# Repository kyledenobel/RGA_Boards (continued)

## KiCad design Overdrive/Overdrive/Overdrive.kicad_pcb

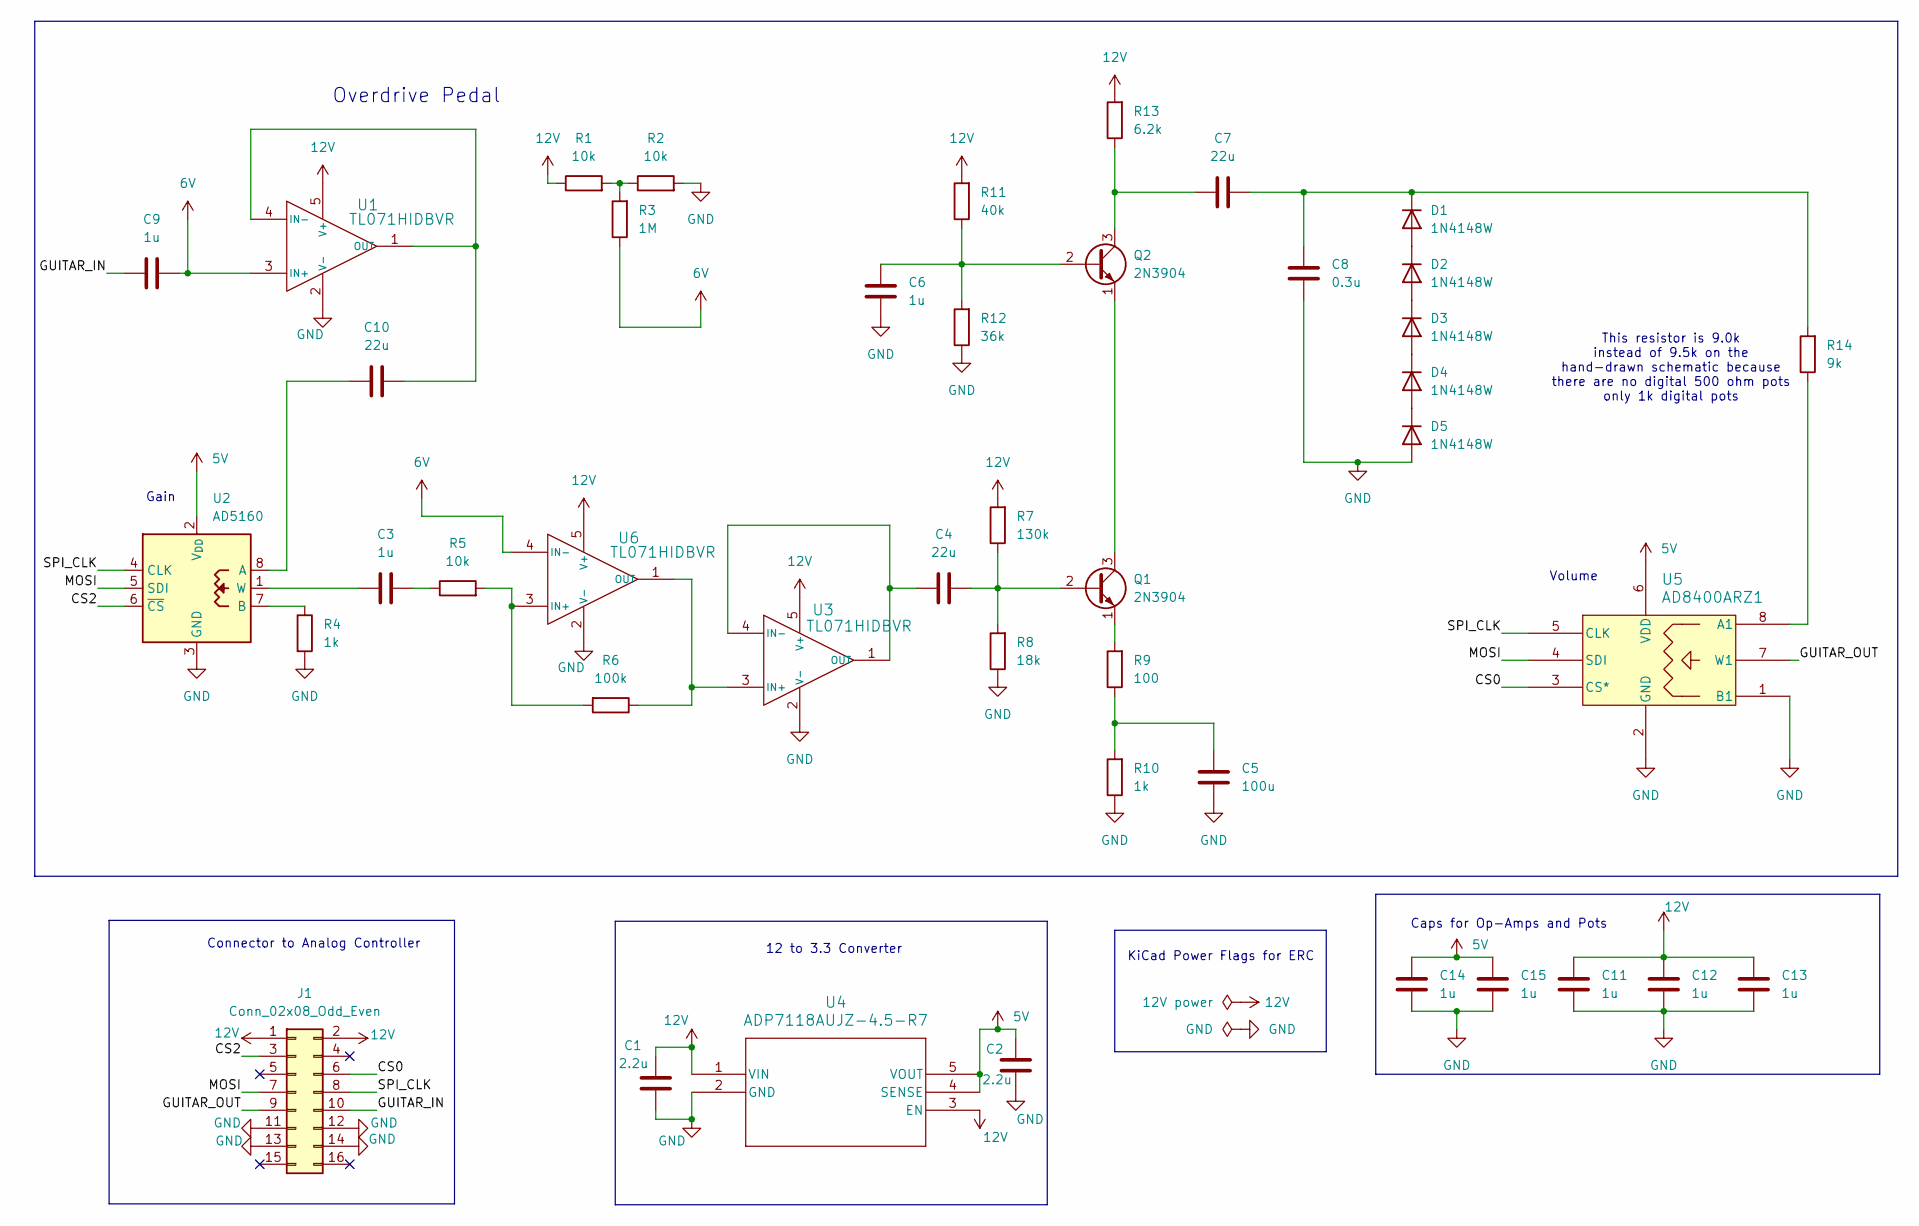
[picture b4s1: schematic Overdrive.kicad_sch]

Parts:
C1, C2: 2.2u; C_0603_1608Metric
C3, C6, C9, C11, C12, C13, C14, C15: 1u; C_0603_1608Metric
C4, C7, C10: 22u; C_0603_1608Metric
C5: 100u; C_1206_3216Metric
C8: 0.3u; C_0603_1608Metric
D1, D2, D3, D4, D5: 1N4148W; D_SOD-123
J1: Conn_02x08_Odd_Even; PinHeader_2x08_P2.54mm_Horizontal
Q1, Q2: 2N3904; TO-92_Inline
R1, R2, R5: 10k; R_0603_1608Metric
R3: 1M; R_0603_1608Metric
R4, R10: 1k; R_0603_1608Metric
R6: 100k; R_0603_1608Metric
R7: 130k; R_0603_1608Metric
R8: 18k; R_0603_1608Metric
R9: 100; R_0603_1608Metric
R11: 40k; R_0603_1608Metric
R12: 36k; R_0603_1608Metric
R13: 6.2k; R_0603_1608Metric
R14: 9k; R_0603_1608Metric
U1, U3, U6: TL071HIDBVR
U2: AD5160; SOT-23-8
U4: ADP7118AUJZ-4.5-R7; UJ-5_ADI
U5: AD8400ARZ1; R_8_ADI

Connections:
5V: C2.1, C14.2, C15.2, U2.2 (V_{DD}), U4.4 (SENSE), U4.5 (VOUT), U5.6 (VDD)
6V: C9.2, R3.1, U1.3 (IN+), U6.4 (IN-)
12V: C1.1, C11.2, C12.2, C13.2, J1.1, J1.2, R1.1, R7.2, R11.2, R13.2, U1.5 (V+), U3.5 (V+), U4.1 (VIN), U4.3 (EN), U6.5 (V+)
/CS0: J1.6, U5.3 (CS*)
/CS2: J1.3, U2.6 (~CS)
/GUITAR_IN: C9.1, J1.10
/GUITAR_OUT: J1.9, U5.7 (W1)
/MOSI: J1.7, U2.5 (SDI), U5.4 (SDI)
/SPI_CLK: J1.8, U2.4 (CLK), U5.5 (CLK)
GND: C1.2, C2.2, C5.1, C6.1, C8.1, C11.1, C12.1, C13.1, C14.1, C15.1, D5.2 (A), J1.11, J1.12, J1.13, J1.14, R2.2, R4.2, R8.1, R10.1, R12.1, U1.2 (V-), U2.3 (GND), U3.2 (V-), U4.2 (GND), U5.1 (B1), U5.2 (GND), U6.2 (V-)
unnamed: C3.2, R5.1
unnamed: C5.2, R9.1, R10.2
unnamed: D1.2 (A), D2.1 (K)
unnamed: C7.2, C8.2, D1.1 (K), R14.2
unnamed: D2.2 (A), D3.1 (K)
unnamed: D3.2 (A), D4.1 (K)
unnamed: D4.2 (A), D5.1 (K)
unnamed: C4.2, Q1.2 (B), R7.1, R8.2
unnamed: Q1.3 (C), Q2.1 (E)
unnamed: Q1.1 (E), R9.2
unnamed: C6.2, Q2.2 (B), R11.1, R12.2
unnamed: C7.1, Q2.3 (C), R13.1
unnamed: R1.2, R2.1, R3.2
unnamed: C10.2, U1.1 (OUT), U1.4 (IN-)
unnamed: C10.1, U2.8 (A)
unnamed: R4.1, U2.7 (B)
unnamed: C3.1, U2.1 (W)
unnamed: R6.1, U3.3 (IN+), U6.1 (OUT)
unnamed: C4.1, U3.1 (OUT), U3.4 (IN-)
unnamed: R14.1, U5.8 (A1)
unnamed: R5.2, R6.2, U6.3 (IN+)

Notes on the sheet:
Volume
Connector to Analog Controller
12 to 3.3 Converter
This resistor is 9.0k instead of 9.5k on the hand-drawn schematic because there are no digital 500 ohm pots only 1k digital pots
Gain
Overdrive Pedal
KiCad Power Flags for ERC
Caps for Op-Amps and Pots

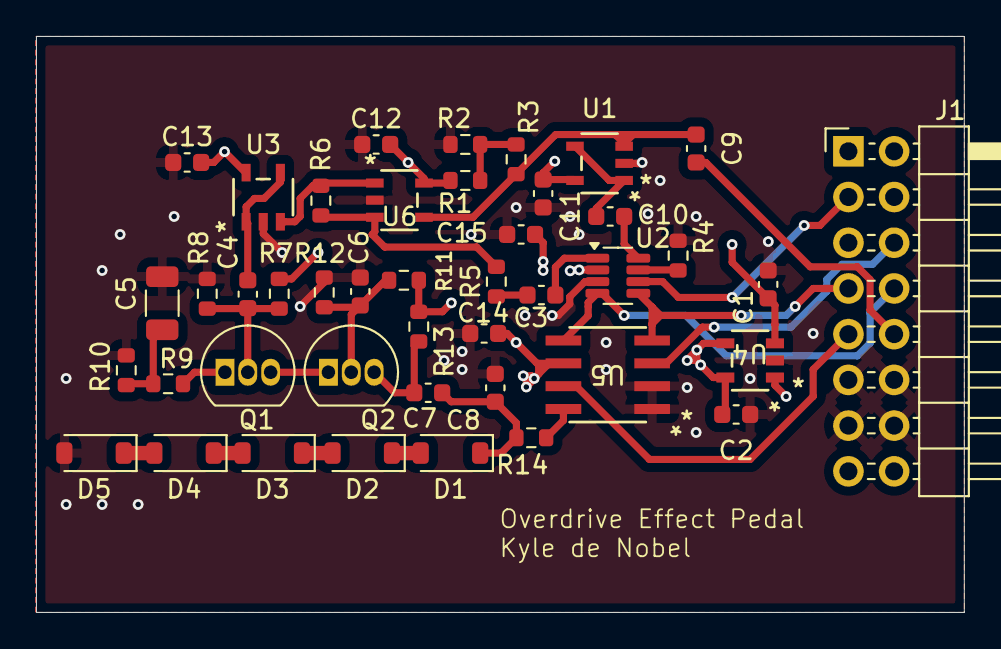
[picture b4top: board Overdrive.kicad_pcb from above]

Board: 4 copper layers, 51.5 x 32.0 mm, 43 parts (0 on the bottom side), 31 nets.

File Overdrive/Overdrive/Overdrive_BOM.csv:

Reference,Qty,Value,DNP,Exclude from BOM,Exclude from Board,Footprint,Datasheet
"C1,C2",2,2.2u,,,,Capacitor_SMD:C_0603_1608Metric,~
"C3,C6,C9,C11,C12,C13,C14,C15",8,1u,,,,Capacitor_SMD:C_0603_1608Metric,~
"C4,C7,C10",3,22u,,,,Capacitor_SMD:C_0603_1608Metric,~
C5,1,100u,,,,Capacitor_SMD:C_1206_3216Metric,~
C8,1,0.3u,,,,Capacitor_SMD:C_0603_1608Metric,~
"D1,D2,D3,D4,D5",5,1N4148W,,,,Diode_SMD:D_SOD-123,https://www.vishay.com/docs/85748/1n4148w.pdf
J1,1,Conn_02x08_Odd_Even,,,,Connector_PinHeader_2.54mm:PinHeader_2x08_P2.54mm_Horizontal,~
"Q1,Q2",2,2N3904,,,,Package_TO_SOT_THT:TO-92_Inline,https://www.onsemi.com/pub/Collateral/2N3903-D.PDF
"R1,R2,R5",3,10k,,,,Resistor_SMD:R_0603_1608Metric,~
R3,1,1M,,,,Resistor_SMD:R_0603_1608Metric,~
"R4,R10",2,1k,,,,Resistor_SMD:R_0603_1608Metric,~
R6,1,100k,,,,Resistor_SMD:R_0603_1608Metric,~
R7,1,130k,,,,Resistor_SMD:R_0603_1608Metric,~
R8,1,18k,,,,Resistor_SMD:R_0603_1608Metric,~
R9,1,100,,,,Resistor_SMD:R_0603_1608Metric,~
R11,1,40k,,,,Resistor_SMD:R_0603_1608Metric,~
R12,1,36k,,,,Resistor_SMD:R_0603_1608Metric,~
R13,1,6.2k,,,,Resistor_SMD:R_0603_1608Metric,~
R14,1,9k,,,,Resistor_SMD:R_0603_1608Metric,~
"U1,U3,U6",3,TL071HIDBVR,,,,TL071:TL071HIDBVR,https://www.ti.com/lit/gpn/tl071h
U2,1,AD5160,,,,Package_TO_SOT_SMD:SOT-23-8,https://www.analog.com/media/en/technical-documentation/data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
U4,1,ADP7118AUJZ-4.5-R7,,,,ADP7118AUJZ-4-5-R7:UJ-5_ADI,https://www.analog.com/media/en/technical-documentation/data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
U5,1,AD8400ARZ1,,,,footprints:R_8_ADI,https://www.digikey.com/en/products/detail/analog-devices-in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

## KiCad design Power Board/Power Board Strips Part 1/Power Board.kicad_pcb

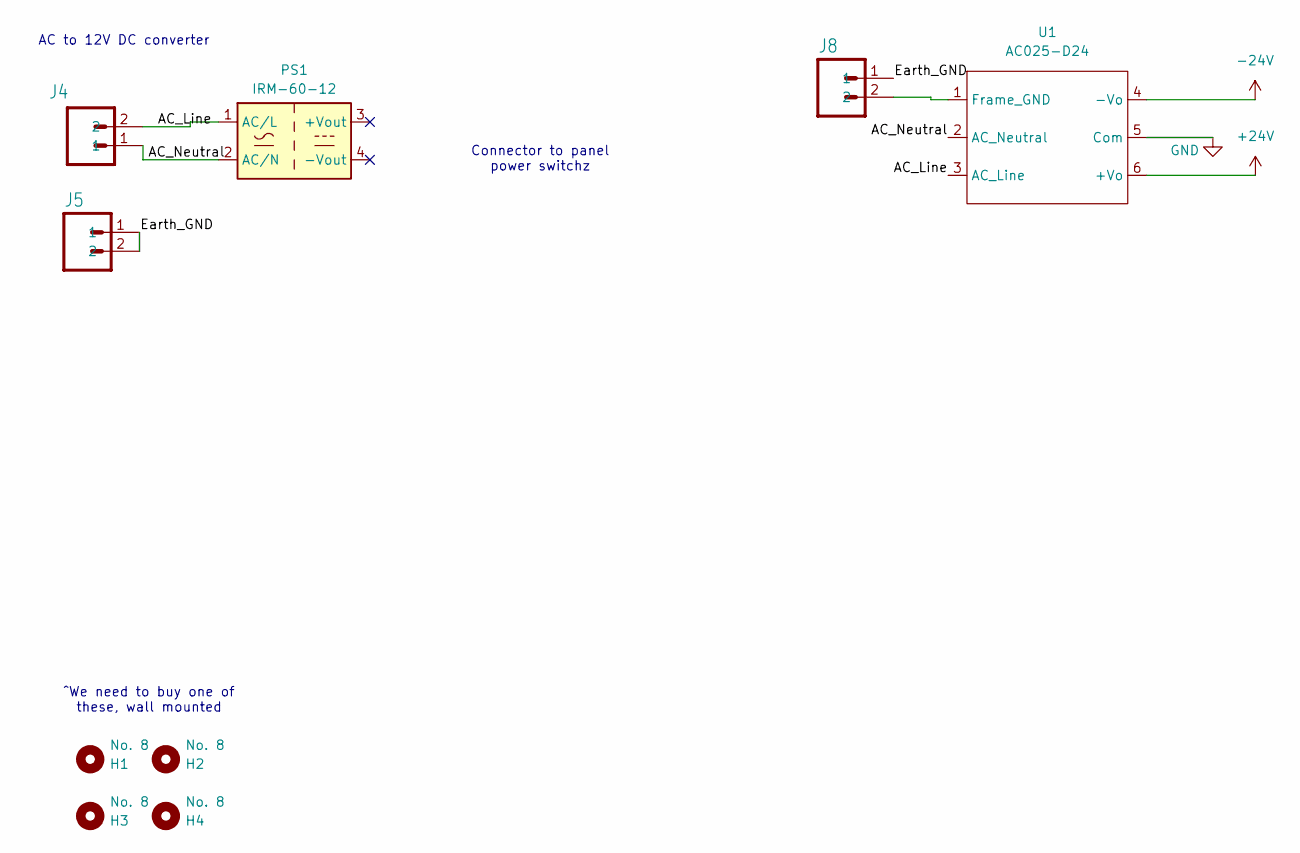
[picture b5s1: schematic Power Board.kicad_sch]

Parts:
H1, H2, H3, H4: No. 8; MountingHole_3.2mm_M3
J4: MEGAFIT-2-VERT; Molex_Mega-Fit_76829-0102_2x01_P5.70mm_Vertical
J5: MINIFIT-2-VERT; Molex_Micro-Fit_3.0_43650-0215_1x02_P3.00mm_Vertical
J8: MINIFIT-2-VERT; PinHeader_1x02_P2.54mm_Vertical
PS1: IRM-60-12; Converter_ACDC_MeanWell_IRM-60-xx_THT
U1: AC025-D24; AC025-D15

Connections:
+24V: U1.6 (+Vo)
-24V: U1.4 (-Vo)
/AC_Line: J4.2, PS1.1 (AC/L), U1.3 (AC_Line)
/AC_Neutral: J4.1, PS1.2 (AC/N), U1.2 (AC_Neutral)
/Earth_GND: J5.1, J5.2, J8.1
GND: U1.5 (Com)
unnamed: J8.2, U1.1 (Frame_GND)

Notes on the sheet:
AC to 12V DC converter
Connector to panel power switchz
^We need to buy one of these, wall mounted

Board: 4 copper layers, 9 parts (0 on the bottom side), 4 nets, no tracks yet.

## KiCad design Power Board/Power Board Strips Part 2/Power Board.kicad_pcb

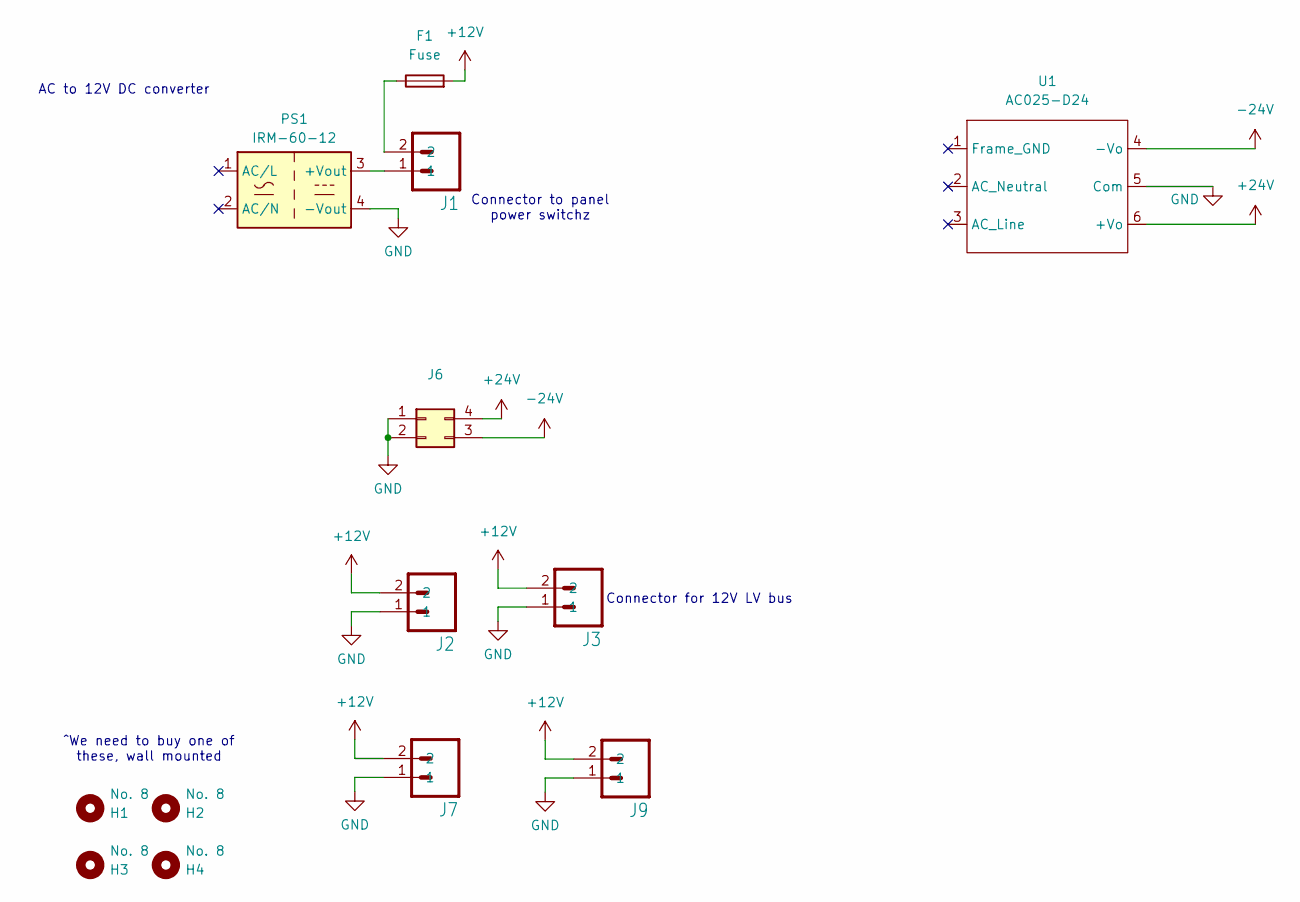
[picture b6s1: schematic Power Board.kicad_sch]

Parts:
F1: Fuse; Fuseholder_Blade_Mini_Keystone_3568
H1, H2, H3, H4: No. 8; MountingHole_3.2mm_M3
J1: MINIFIT-2-VERT; Molex_Mega-Fit_76829-0102_2x01_P5.70mm_Vertical
J2, J3, J7, J9: MINIFIT-2-VERT; Molex_Mini-Fit_Jr_5566-02A_2x01_P4.20mm_Vertical
J6: Molex_Mega-Fit_76829-0004_2x02_P5.70mm_Vertical
PS1: IRM-60-12; Converter_ACDC_MeanWell_IRM-60-xx_THT
U1: AC025-D24; AC025-D15

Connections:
+12V: F1.2, J2.2, J3.2, J7.2, J9.2
+24V: J6.4, U1.6 (+Vo)
-24V: J6.3, U1.4 (-Vo)
GND: J2.1, J3.1, J6.1, J6.2, J7.1, J9.1, PS1.4 (-Vout), U1.5 (Com)
unnamed: F1.1, J1.2
unnamed: J1.1, PS1.3 (+Vout)

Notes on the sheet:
AC to 12V DC converter
Connector to panel power switchz
^We need to buy one of these, wall mounted
Connector for 12V LV bus

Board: 4 copper layers, 13 parts (0 on the bottom side), 6 nets, no tracks yet.

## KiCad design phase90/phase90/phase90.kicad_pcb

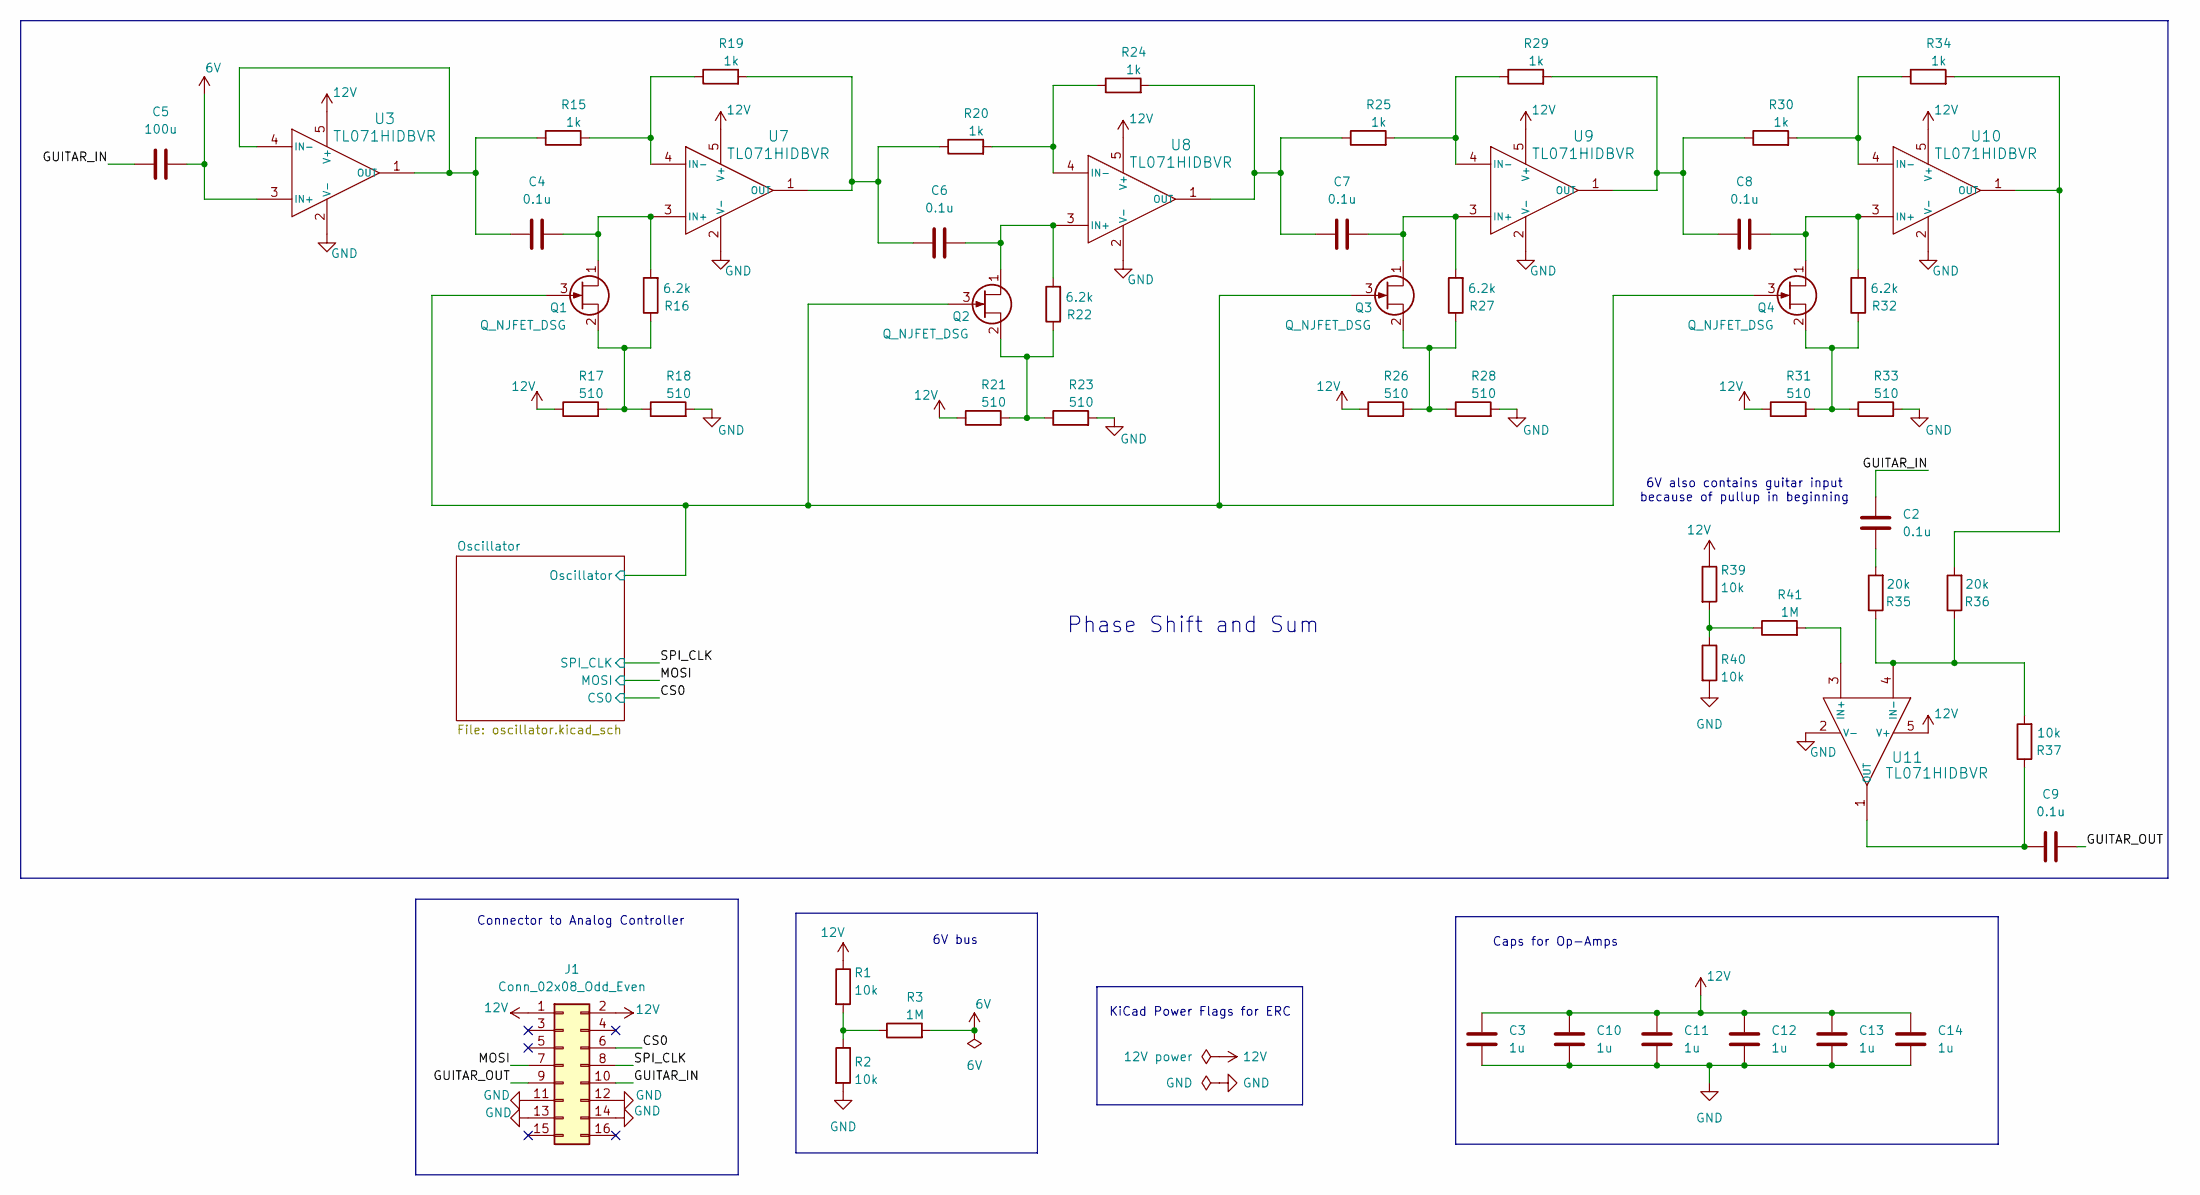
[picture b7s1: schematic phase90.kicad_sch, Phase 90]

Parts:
C2, C4, C6, C7, C8, C9: 0.1u; C_0603_1608Metric
C3, C10, C11, C12, C13, C14: 1u; C_0603_1608Metric
C5: 100u; C_0603_1608Metric
J1: Conn_02x08_Odd_Even; PinHeader_2x08_P2.54mm_Horizontal
Q1, Q2, Q3, Q4: Q_NJFET_DSG; TO-92
R1, R2, R37, R39, R40: 10k; R_0603_1608Metric
R3, R41: 1M; R_0603_1608Metric
R15, R19, R20, R24, R25, R29, R30, R34: 1k; R_0603_1608Metric
R16, R22, R27, R32: 6.2k; R_0603_1608Metric
R17, R18, R21, R23, R26, R28, R31, R33: 510; R_0603_1608Metric
R35, R36: 20k; R_0603_1608Metric
U3, U7, U8, U9, U10, U11: TL071HIDBVR; SOT-23-5

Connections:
6V: C5.2, R3.2, U3.3 (IN+)
12V: C3.1, C10.1, C11.1, C12.1, C13.1, C14.1, J1.1, J1.2, R1.1, R17.1, R21.1, R26.1, R31.1, R39.1, U3.5 (V+), U7.5 (V+), U8.5 (V+), U9.5 (V+), U10.5 (V+), U11.5 (V+); also elsewhere on the board
/CS0: J1.6; also elsewhere on the board
/GUITAR_IN: C2.2, C5.1, J1.10
/GUITAR_OUT: C9.2, J1.9
/MOSI: J1.7; also elsewhere on the board
/Oscillator/Oscillator: Q1.3 (G), Q2.3 (G), Q3.3 (G), Q4.3 (G); also elsewhere on the board
/SPI_CLK: J1.8; also elsewhere on the board
GND: C3.2, C10.2, C11.2, C12.2, C13.2, C14.2, J1.11, J1.12, J1.13, J1.14, R2.2, R18.2, R23.2, R28.2, R33.2, R40.2, U3.2 (V-), U7.2 (V-), U8.2 (V-), U9.2 (V-), U10.2 (V-), U11.2 (V-); also elsewhere on the board
unnamed: C2.1, R35.2
unnamed: C4.2, Q1.1 (D), R16.2, U7.3 (IN+)
unnamed: Q1.2 (S), R16.1, R17.2, R18.1
unnamed: C6.2, Q2.1 (D), R22.2, U8.3 (IN+)
unnamed: Q2.2 (S), R21.2, R22.1, R23.1
unnamed: C7.2, Q3.1 (D), R27.2, U9.3 (IN+)
unnamed: Q3.2 (S), R26.2, R27.1, R28.1
unnamed: C8.2, Q4.1 (D), R32.2, U10.3 (IN+)
unnamed: Q4.2 (S), R31.2, R32.1, R33.1
unnamed: R1.2, R2.1, R3.1
unnamed: R39.2, R40.1, R41.1
unnamed: C4.1, R15.1, U3.1 (OUT), U3.4 (IN-)
unnamed: R15.2, R19.1, U7.4 (IN-)
unnamed: C6.1, R19.2, R20.1, U7.1 (OUT)
unnamed: R20.2, R24.1, U8.4 (IN-)
unnamed: C7.1, R24.2, R25.1, U8.1 (OUT)
unnamed: R25.2, R29.1, U9.4 (IN-)
unnamed: C8.1, R29.2, R30.1, U9.1 (OUT)
unnamed: R30.2, R34.1, U10.4 (IN-)
unnamed: R34.2, R36.2, U10.1 (OUT)
unnamed: R41.2, U11.3 (IN+)
unnamed: R35.1, R36.1, R37.2, U11.4 (IN-)
unnamed: C9.1, R37.1, U11.1 (OUT)

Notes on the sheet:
KiCad Power Flags for ERC
Caps for Op-Amps
6V also contains guitar input because of pullup in beginning
Phase Shift and Sum
6V bus
Connector to Analog Controller

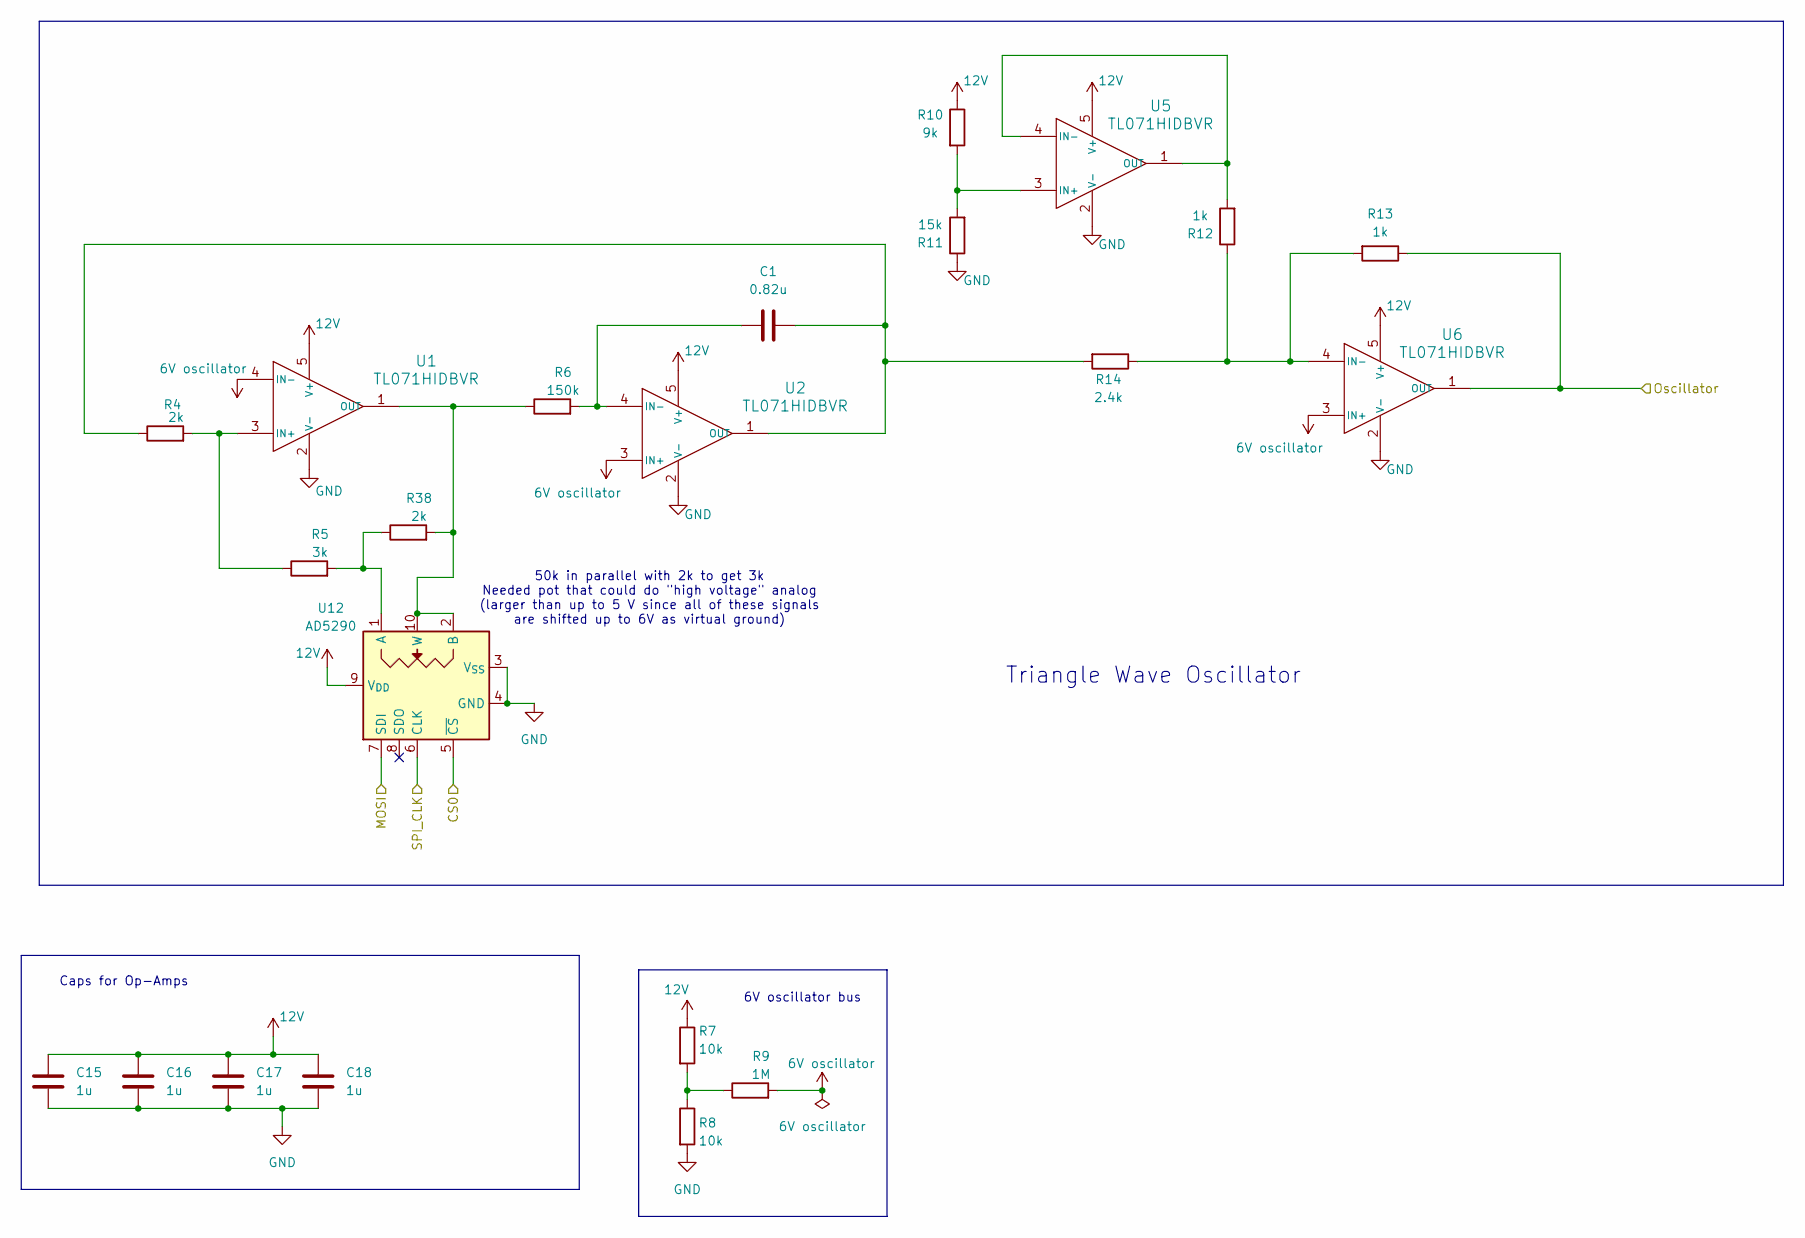
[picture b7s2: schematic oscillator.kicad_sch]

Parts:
C1: 0.82u; C_0603_1608Metric
C15, C16, C17, C18: 1u; C_0603_1608Metric
R4, R38: 2k; R_0603_1608Metric
R5: 3k; R_0603_1608Metric
R6: 150k; R_0603_1608Metric
R7, R8: 10k; R_0603_1608Metric
R9: 1M; R_0603_1608Metric
R10: 9k; R_0603_1608Metric
R11: 15k; R_0603_1608Metric
R12, R13: 1k; R_0603_1608Metric
R14: 2.4k; R_0603_1608Metric
U1, U2, U5, U6: TL071HIDBVR; SOT-23-5
U12: AD5290; MSOP-10_3x3mm_P0.5mm

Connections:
6V oscillator: R9.2, U1.4 (IN-), U2.3 (IN+), U6.3 (IN+)
12V: C15.1, C16.1, C17.1, C18.1, R7.1, R10.1, U1.5 (V+), U2.5 (V+), U5.5 (V+), U6.5 (V+), U12.9 (V_{DD}); also elsewhere on the board
/CS0: U12.5 (~CS); also elsewhere on the board
/MOSI: U12.7 (SDI); also elsewhere on the board
/Oscillator/Oscillator: R13.1, U6.1 (OUT); also elsewhere on the board
/SPI_CLK: U12.6 (CLK); also elsewhere on the board
GND: C15.2, C16.2, C17.2, C18.2, R8.2, R11.1, U1.2 (V-), U2.2 (V-), U5.2 (V-), U6.2 (V-), U12.3 (V_{SS}), U12.4 (GND); also elsewhere on the board
unnamed: R7.2, R8.1, R9.1
unnamed: R4.2, R5.1, U1.3 (IN+)
unnamed: R6.1, R38.2, U1.1 (OUT), U12.2 (B), U12.10 (W)
unnamed: C1.1, R6.2, U2.4 (IN-)
unnamed: C1.2, R4.1, R14.2, U2.1 (OUT)
unnamed: R10.2, R11.2, U5.3 (IN+)
unnamed: R12.2, U5.1 (OUT), U5.4 (IN-)
unnamed: R12.1, R13.2, R14.1, U6.4 (IN-)
unnamed: R5.2, R38.1, U12.1 (A)

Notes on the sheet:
Triangle Wave Oscillator
6V oscillator bus
Caps for Op-Amps
50k in parallel with 2k to get 3k Needed pot that could do "high voltage" analog (larger than up to 5 V since all of these signals are shifted up to 6V as virtual ground)

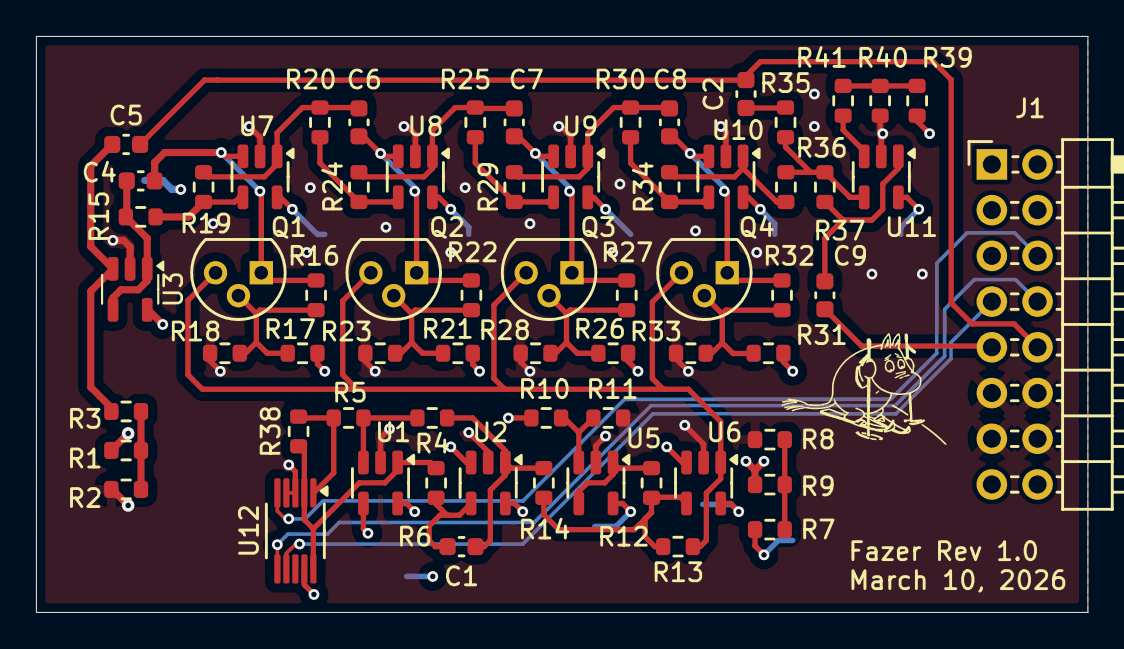
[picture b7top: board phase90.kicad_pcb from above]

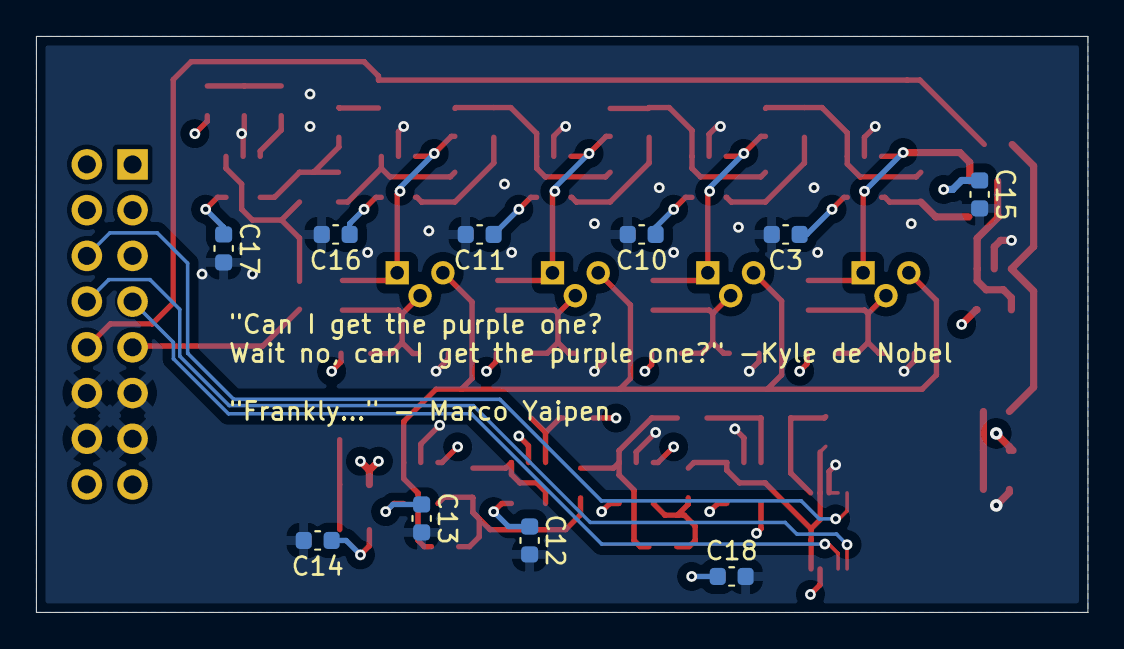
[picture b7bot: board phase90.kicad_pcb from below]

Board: 4 copper layers, 58.4 x 32.0 mm, 75 parts (10 on the bottom side), 42 nets.

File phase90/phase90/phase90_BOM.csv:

Reference,Qty,Value,DNP,Exclude from BOM,Exclude from Board,Footprint,Datasheet
C1,1,0.82u,,,,Capacitor_SMD:C_0603_1608Metric,~
"C2,C4,C6,C7,C8,C9",6,0.1u,,,,Capacitor_SMD:C_0603_1608Metric,~
"C3,C10,C11,C12,C13,C14,C15,C16,C17,C18",10,1u,,,,Capacitor_SMD:C_0603_1608Metric,~
C5,1,100u,,,,Capacitor_SMD:C_0603_1608Metric,~
J1,1,Conn_02x08_Odd_Even,,,,Connector_PinHeader_2.54mm:PinHeader_2x08_P2.54mm_Horizontal,~
"Q1,Q2,Q3,Q4",4,Q_NJFET_DSG,,,,Package_TO_SOT_THT:TO-92,~
"R1,R2,R7,R8,R37,R39,R40",7,10k,,,,Resistor_SMD:R_0603_1608Metric,~
"R3,R9,R41",3,1M,,,,Resistor_SMD:R_0603_1608Metric,~
"R4,R38",2,2k,,,,Resistor_SMD:R_0603_1608Metric,~
R5,1,3k,,,,Resistor_SMD:R_0603_1608Metric,~
R6,1,150k,,,,Resistor_SMD:R_0603_1608Metric,~
R10,1,9k,,,,Resistor_SMD:R_0603_1608Metric,~
R11,1,15k,,,,Resistor_SMD:R_0603_1608Metric,~
"R12,R13,R15,R19,R20,R24,R25,R29,R30,R34",10,1k,,,,Resistor_SMD:R_0603_1608Metric,~
R14,1,2.4k,,,,Resistor_SMD:R_0603_1608Metric,~
"R16,R22,R27,R32",4,6.2k,,,,Resistor_SMD:R_0603_1608Metric,~
"R17,R18,R21,R23,R26,R28,R31,R33",8,510,,,,Resistor_SMD:R_0603_1608Metric,~
"R35,R36",2,20k,,,,Resistor_SMD:R_0603_1608Metric,~
"U1,U2,U3,U5,U6,U7,U8,U9,U10,U11",10,TL071HIDBVR,,,,Package_TO_SOT_SMD:SOT-23-5,https://www.ti.com/lit/gpn/tl071h
U12,1,AD5290,,,,Package_SO:MSOP-10_3x3mm_P0.5mm,https://www.digikey.com/en/products/detail/analog-devices-in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
